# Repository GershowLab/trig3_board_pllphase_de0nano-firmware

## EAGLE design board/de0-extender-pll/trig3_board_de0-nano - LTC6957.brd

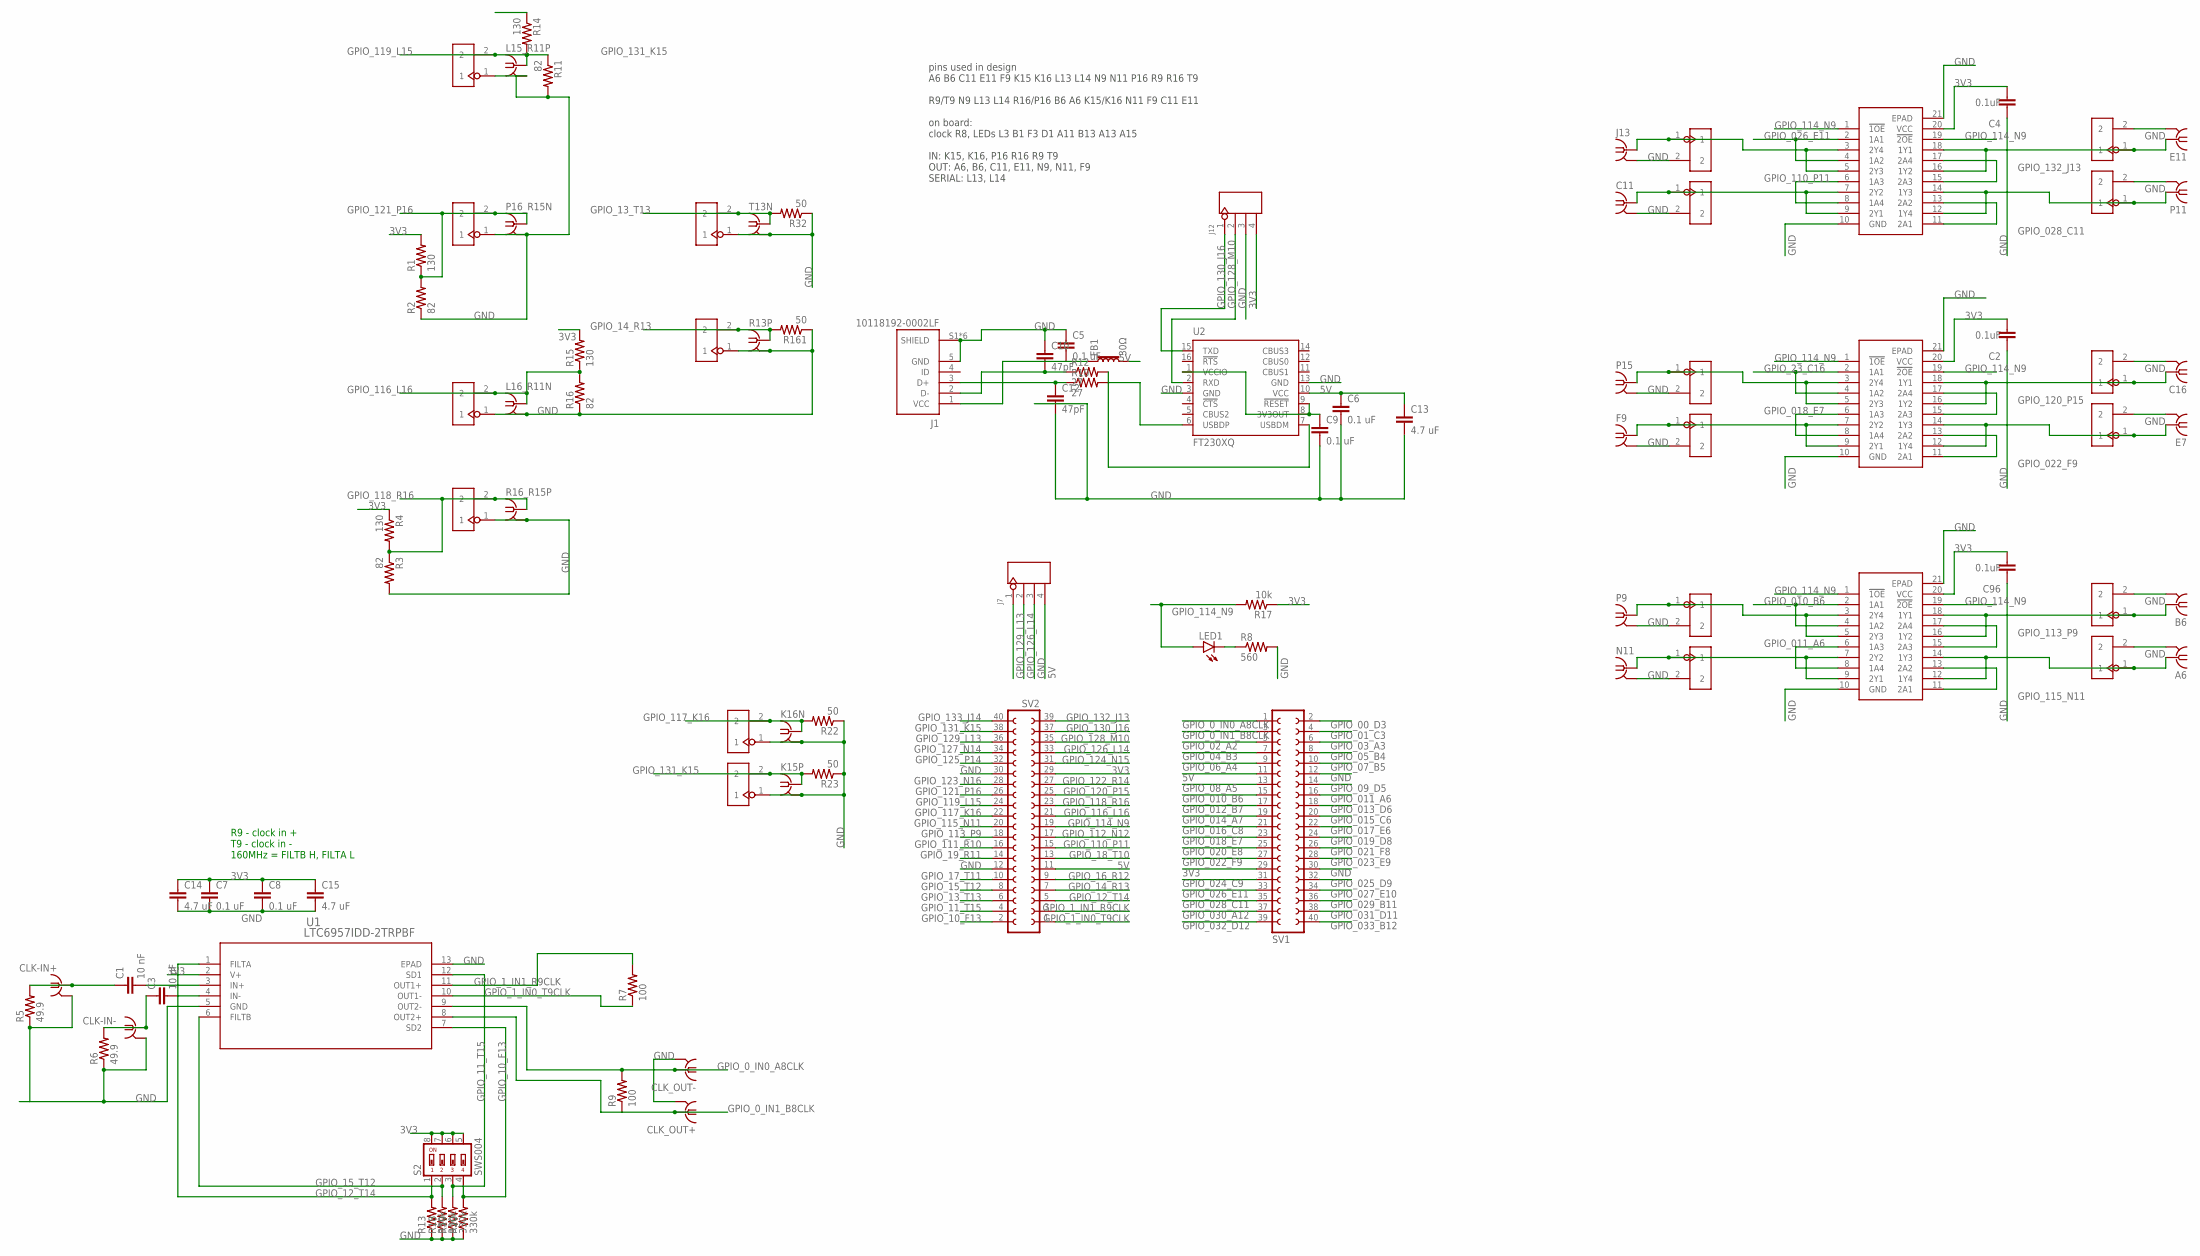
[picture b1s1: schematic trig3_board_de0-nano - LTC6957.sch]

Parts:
A6: BU-SMB-V; LCSC_PART# C496549
B6: BU-SMB-V; LCSC_PART# C496549
C1, C3: 10 nF; C0603; LCSC_PART# C57112
C2, C4, C96: 0.1uF; C0603; LCSC_PART# C14663
C5, C6, C7, C8, C9: 0.1 uF; C0603; LCSC_PART# C14663
C10, C12: 47pF; C0603; LCSC_PART# C1671
C11, C16: BU-SMB-V; LCSC_PART# C496549
C13, C14, C15: 4.7 uF; C0603; LCSC_PART# C19666
CLK-IN+: BU-SMB-V; LCSC_PART# C496549
CLK-IN-: BU-SMB-V; LCSC_PART# C496549
CLK_OUT+: BU-SMB-V; LCSC_PART# C496549
CLK_OUT-: BU-SMB-V; LCSC_PART# C496549
E7, E11: BU-SMB-V; LCSC_PART# C496549
F9: BU-SMB-V; LCSC_PART# C496549
FB1: 30Ω; 0603; LCSC_PART# C1002
J1: 10118192-0002LF; AMPHENOL_10118192-0002LF; LCSC_PART# C132564
J7, J12: 4p-2.54; H4-2.54
J13: BU-SMB-V; LCSC_PART# C496549
J17, J23, J24, J32, J34, J38, J42, J43: 2p-2.54; H2-2.54
K15P, K16N: BU-SMB-V; LCSC_PART# C496549
L15_R11P, L16_R11N: BU-SMB-V; LCSC_PART# C496549
LED1: red; SML0805; LCSC_PART# C84256
N11: BU-SMB-V; LCSC_PART# C496549
OJ41, OJ42, OJ43, OJ44, OJ57, OJ58, OJ59, OJ60, OJ73, OJ74, OJ75, OJ76: 2p-2.54; H2-2.54
P9, P11, P15, P16_R15N: BU-SMB-V; LCSC_PART# C496549
R1, R4, R14, R15: 130; R0603; LCSC_PART# C22796
R2, R3, R11, R16: 82; R0603; LCSC_PART# C23255
R5, R6: 49.9; R0603; LCSC_PART# C23185
R7, R9: 100; R0603; LCSC_PART# C22775
R8: 560; R0805; LCSC_PART# C28636
R10, R12: 27; R0603; LCSC_PART# C25190
R13, R18, R19, R20: 330k; R0603; LCSC_PART# C23137
R13P, R16_R15P: BU-SMB-V; LCSC_PART# C496549
R17: 10k; AXIAL-0.3
R22, R23, R32, R161: 50; AXIAL-0.3
S2: SWS004; SMS-004; LCSC_PART# C221954
SV1, SV2: FE20-2
T13N: BU-SMB-V; LCSC_PART# C496549
U1: LTC6957IDD-2TRPBF; DFN-12_DD_LIT; LCSC_PART# C689878
U2: FT230XQ; QFN16; LCSC_PART# C128629
U3, U4, U5: SN74LVTH244ARGYR; RGY20_3P05X2P05; LCSC_PART# C2869480

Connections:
3V3: C2.2, C4.2, C7.1, C8.1, C14.1, C15.1, C96.2, J12.4, R1.2, R4.1, R14.1, R15.2, R17.P$1 (1), S2.5, S2.6, S2.7, S2.8, SV1.29, SV2.29, U1.2 (V+), U3.20 (VCC), U4.20 (VCC), U5.20 (VCC)
5V: C6.1, C13.1, FB1.2, J7.4, SV1.11, SV2.11, U2.10 (VCC)
GND: A6.2, A6.3 (2), A6.4 (2), A6.5 (2), B6.2, B6.3 (2), B6.4 (2), B6.5 (2), C2.1, C4.1, C5.1, C6.2, C7.2, C8.2, C9.2, C10.1, C11.2, C11.3 (2), C11.4 (2), C11.5 (2), C12.2, C13.2, C14.2, C15.2, C16.2, C16.3 (2), C16.4 (2), C16.5 (2), C96.1, CLK-IN+.2, CLK-IN+.3 (2), CLK-IN+.4 (2), CLK-IN+.5 (2), CLK-IN-.2, CLK-IN-.3 (2), CLK-IN-.4 (2), CLK-IN-.5 (2), CLK_OUT+.2, CLK_OUT+.3 (2), CLK_OUT+.4 (2), CLK_OUT+.5 (2), CLK_OUT-.2, CLK_OUT-.3 (2), CLK_OUT-.4 (2), CLK_OUT-.5 (2), E7.2, E7.3 (2), E7.4 (2), E7.5 (2), E11.2, E11.3 (2), E11.4 (2), E11.5 (2), F9.2, F9.3 (2), F9.4 (2), F9.5 (2), J1.5 (GND), J1.S1 (SHIELD), J1.S2 (SHIELD), J1.S3 (SHIELD), J1.S4 (SHIELD), J1.S5 (SHIELD), J1.S6 (SHIELD), J7.3, J12.3, J13.2, J13.3 (2), J13.4 (2), J13.5 (2), J17.1, J23.1, J24.1, J32.1, J34.1, J38.1, J42.1, J43.1, K15P.2, K15P.3 (2), K15P.4 (2), K15P.5 (2), K16N.2, K16N.3 (2), K16N.4 (2), K16N.5 (2), L15_R11P.2, L15_R11P.3 (2), L15_R11P.4 (2), L15_R11P.5 (2), L16_R11N.2, L16_R11N.3 (2), L16_R11N.4 (2), L16_R11N.5 (2), N11.2, N11.3 (2), N11.4 (2), N11.5 (2), OJ41.2, OJ42.2, OJ43.2, OJ44.2, OJ57.2, OJ58.2, OJ59.2, OJ60.2, OJ73.2, OJ74.2, OJ75.2, OJ76.2, P9.2, P9.3 (2), P9.4 (2), P9.5 (2), P11.2, P11.3 (2), P11.4 (2), P11.5 (2), P15.2, P15.3 (2), P15.4 (2), P15.5 (2), P16_R15N.2, P16_R15N.3 (2), P16_R15N.4 (2), P16_R15N.5 (2), R2.1, R3.2, R5.1, R6.1, R8.2, R11.2, R13.1, R13P.2, R13P.3 (2), R13P.4 (2), R13P.5 (2), R16.1, R16_R15P.2, R16_R15P.3 (2), R16_R15P.4 (2), R16_R15P.5 (2), R18.1, R19.1, R20.1, R22.P$1 (1), R23.P$1 (1), R32.P$1 (1), R161.P$1 (1), SV1.12, SV1.30, SV2.12, SV2.30, T13N.2, T13N.3 (2), T13N.4 (2), T13N.5 (2), U1.5 (GND), U1.13 (EPAD), U2.3 (GND), U2.13 (GND), U3.10 (GND), U3.21 (EPAD), U4.10 (GND), U4.21 (EPAD), U5.10 (GND), U5.21 (EPAD)
GPIO_00_D3: SV1.2
GPIO_0_IN0_A8CLK: CLK_OUT-.1, R9.2, SV1.1, U1.9 (OUT2-)
GPIO_0_IN1_B8CLK: CLK_OUT+.1, R9.1, SV1.3, U1.8 (OUT2+)
GPIO_01_C3: SV1.4
GPIO_1_IN0_T9CLK: R7.1, SV2.1, U1.10 (OUT1-)
GPIO_1_IN1_R9CLK: R7.2, SV2.3, U1.11 (OUT1+)
GPIO_02_A2: SV1.5
GPIO_03_A3: SV1.6
GPIO_04_B3: SV1.7
GPIO_05_B4: SV1.8
GPIO_06_A4: SV1.9
GPIO_07_B5: SV1.10
GPIO_08_A5: SV1.13
GPIO_09_D5: SV1.14
GPIO_010_B6: SV1.15, U5.2 (1A1), U5.4 (1A2)
GPIO_10_F13: R20.2, S2.4, SV2.2, U1.7 (SD2)
GPIO_011_A6: SV1.16, U5.6 (1A3), U5.8 (1A4)
GPIO_11_T15: R19.2, S2.3, SV2.4, U1.12 (SD1)
GPIO_012_B7: SV1.17
GPIO_12_T14: R13.2, S2.1, SV2.5, U1.1 (FILTA)
GPIO_013_D6: SV1.18
GPIO_13_T13: J38.2, R32.P$2 (2), SV2.6, T13N.1
GPIO_014_A7: SV1.19
GPIO_14_R13: J17.2, R13P.1, R161.P$2 (2), SV2.7
GPIO_015_C6: SV1.20
GPIO_15_T12: R18.2, S2.2, SV2.8, U1.6 (FILTB)
GPIO_016_C8: SV1.21
GPIO_16_R12: SV2.9
GPIO_017_E6: SV1.22
GPIO_17_T11: SV2.10
GPIO_018_E7: SV1.23, U4.6 (1A3), U4.8 (1A4)
GPIO_18_T10: SV2.13
GPIO_019_D8: SV1.24
GPIO_19_R11: SV2.14
GPIO_020_E8: SV1.25
GPIO_021_F8: SV1.26
GPIO_022_F9: SV1.27, U4.11 (2A1), U4.13 (2A2)
GPIO_23_C16: U4.2 (1A1), U4.4 (1A2)
GPIO_023_E9: SV1.28
GPIO_024_C9: SV1.31
GPIO_025_D9: SV1.32
GPIO_026_E11: SV1.33, U3.2 (1A1), U3.4 (1A2)
GPIO_027_E10: SV1.34
GPIO_028_C11: SV1.35, U3.11 (2A1), U3.13 (2A2)
GPIO_029_B11: SV1.36
GPIO_030_A12: SV1.37
GPIO_031_D11: SV1.38
GPIO_032_D12: SV1.39
GPIO_033_B12: SV1.40
GPIO_110_P11: SV2.15, U3.6 (1A3), U3.8 (1A4)
GPIO_111_R10: SV2.16
GPIO_112_N12: SV2.17
GPIO_113_P9: SV2.18, U5.15 (2A3), U5.17 (2A4)
GPIO_114_N9: LED1.A, R17.P$2 (2), SV2.19, U3.1 (!1OE), U3.19 (!2OE), U4.1 (!1OE), U4.19 (!2OE), U5.1 (!1OE), U5.19 (!2OE)
GPIO_115_N11: SV2.20, U5.11 (2A1), U5.13 (2A2)
GPIO_116_L16: J32.2, L16_R11N.1, R15.1, R16.2, SV2.21
GPIO_117_K16: J23.2, K16N.1, R22.P$2 (2), SV2.22
GPIO_118_R16: J34.2, R3.1, R4.2, R16_R15P.1, SV2.23
GPIO_119_L15: J43.2, L15_R11P.1, R11.1, R14.2, SV2.24
GPIO_120_P15: SV2.25, U4.15 (2A3), U4.17 (2A4)
GPIO_121_P16: J42.2, P16_R15N.1, R1.1, R2.2, SV2.26
GPIO_122_R14: SV2.27
GPIO_123_N16: SV2.28
GPIO_124_N15: SV2.31
GPIO_125_P14: SV2.32
GPIO_126_L14: J7.2, SV2.33
GPIO_127_N14: SV2.34
GPIO_128_M10: J12.2, SV2.35, U2.2 (RXD)
GPIO_129_L13: J7.1, SV2.36
GPIO_130_J16: J12.1, SV2.37, U2.15 (TXD)
GPIO_131_K15: J24.2, K15P.1, R23.P$2 (2), SV2.38
GPIO_132_J13: SV2.39, U3.15 (2A3), U3.17 (2A4)
GPIO_133_J14: SV2.40
unnamed: C1.1, CLK-IN+.1, R5.2
unnamed: C3.1, CLK-IN-.1, R6.2
unnamed: C1.2, U1.3 (IN+)
unnamed: C3.2, U1.4 (IN-)
unnamed: C5.2, FB1.1, J1.1 (VCC)
unnamed: C12.1, J1.3 (D+), R10.1
unnamed: LED1.C, R8.1
unnamed: C10.2, J1.2 (D-), R12.1
unnamed: R10.2, U2.6 (USBDP)
unnamed: R12.2, U2.7 (USBDM)
unnamed: C9.1, U2.1 (VCCIO), U2.8 (3V3OUT), U2.9 (!RESET)
OUT21: B6.1, OJ44.1, U5.16 (1Y2), U5.18 (1Y1)
OUT22: A6.1, OJ43.1, U5.12 (1Y4), U5.14 (1Y3)
OUT23: OJ41.1, P9.1, U5.3 (2Y4), U5.5 (2Y3)
OUT24: N11.1, OJ42.1, U5.7 (2Y2), U5.9 (2Y1)
OUT29: C16.1, OJ60.1, U4.16 (1Y2), U4.18 (1Y1)
OUT30: E7.1, OJ59.1, U4.12 (1Y4), U4.14 (1Y3)
OUT31: OJ57.1, P15.1, U4.3 (2Y4), U4.5 (2Y3)
OUT32: F9.1, OJ58.1, U4.7 (2Y2), U4.9 (2Y1)
OUT37: E11.1, OJ76.1, U3.16 (1Y2), U3.18 (1Y1)
OUT38: OJ75.1, P11.1, U3.12 (1Y4), U3.14 (1Y3)
OUT39: J13.1, OJ73.1, U3.3 (2Y4), U3.5 (2Y3)
OUT40: C11.1, OJ74.1, U3.7 (2Y2), U3.9 (2Y1)

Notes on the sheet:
pins used in design A6 B6 C11 E11 F9 K15 K16 L13 L14 N9 N11 P16 R9 R16 T9 R9/T9 N9 L13 L14 R16/P16 B6 A6 K15/K16 N11 F9 C11 E11 on board: clock R8, LEDs L3 B1 F3 D1 A11 B13 A13 A15 IN: K15, K16, P16 R16 R9 T9 OUT: A6, B6, C11, E11, N9, N11, F9 SERIAL: L13, L14
R9 - clock in + T9 - clock in - 160MHz = FILTB H, FILTA L

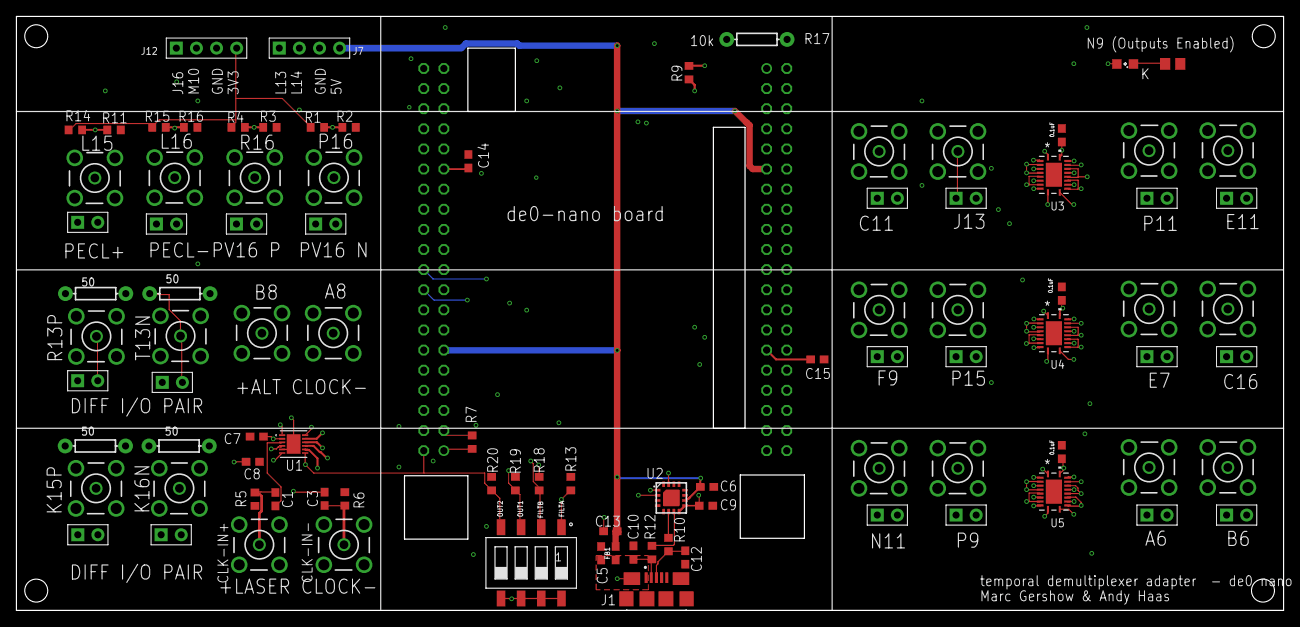
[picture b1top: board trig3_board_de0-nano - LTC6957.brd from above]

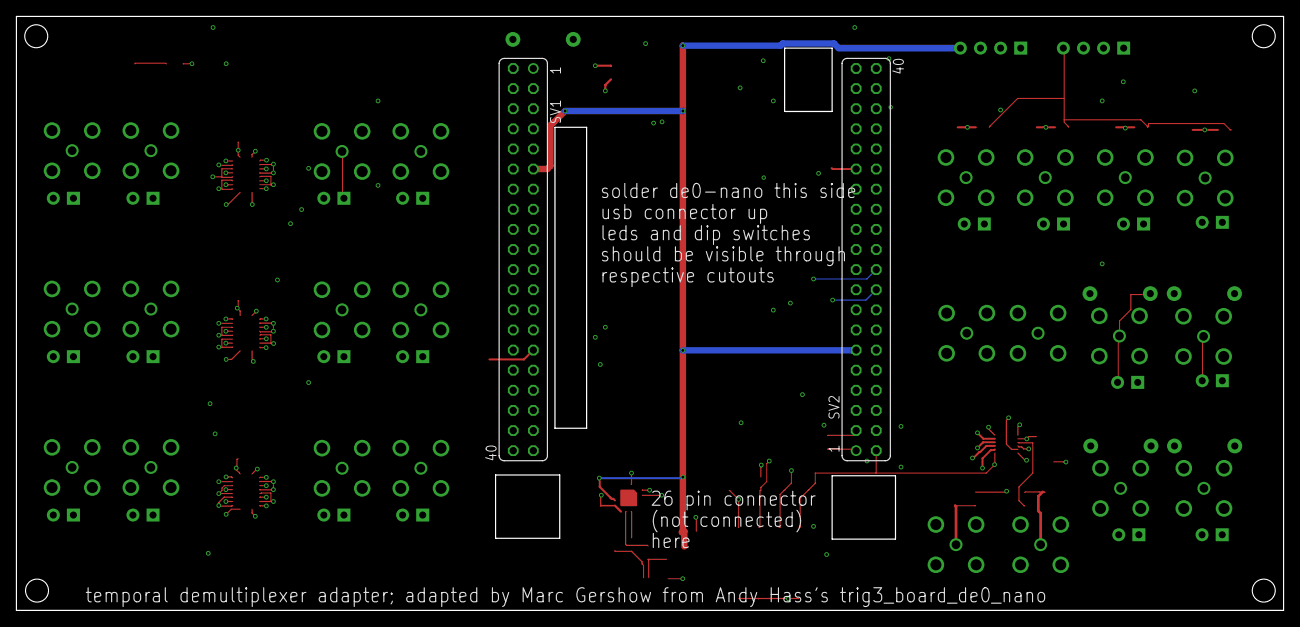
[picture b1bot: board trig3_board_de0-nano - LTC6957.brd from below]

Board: 4 copper layers, 160.0 x 75.0 mm, 96 parts (2 on the bottom side), 59 nets.

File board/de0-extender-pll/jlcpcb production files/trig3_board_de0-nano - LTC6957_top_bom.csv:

Comment,Designator,Footprint,LCSC Part #
0.1 uF,C5 C6 C7 C8 C9,C0603,C14663
0.1uF,C2 C4 C96,C0603,C14663
2p-2.54,J17 J23 J24 J32 J34 J38 J42 J43 OJ41 OJ42 OJ43 OJ44 OJ57 OJ58 OJ59 OJ60 OJ73 OJ74 OJ75 OJ76,H2-2.54,
4.7 uF,C13 C14 C15,C0603,C19666
4p-2.54,J7 J12,H4-2.54,
10 nF,C1 C3,C0603,C57112
10k,R17,AXIAL-0.3,
27,R10 R12,R0603,C25190
30Ω,FB1,0603,C1002
47pF,C10 C12,C0603,C1671
49.9,R5 R6,R0603,C23185
50,R22 R23 R32 R161,AXIAL-0.3,
82,R2 R3 R11 R16,R0603,C23255
100,R7 R9,R0603,C22775
130,R1 R4 R14 R15,R0603,C22796
330k,R13 R18 R19 R20,R0603,C23137
560,R8,R0805,C28636
10118192-0002LF,J1,AMPHENOL_10118192-0002LF,C132564
BU-SMB-V,A6 B6 C11 C16 CLK-IN+ CLK-IN- CLK_OUT+ CLK_OUT- E7 E11 F9 J13 K15P K16N L15_R11P L16_R11N N11 P9 P11 P15 P16_R15N R13P R16_R15P T13N,BU-SMB-V,C496549
FT230XQ,U2,QFN16,C128629
LTC6957IDD-2TRPBF,U1,DFN-12_DD_LIT,C689878
SN74LVTH244ARGYR,U3 U4 U5,RGY20_3P05X2P05,C2869480
SWS004,S2,SMS-004,C221954
red,LED1,SML0805,C84256

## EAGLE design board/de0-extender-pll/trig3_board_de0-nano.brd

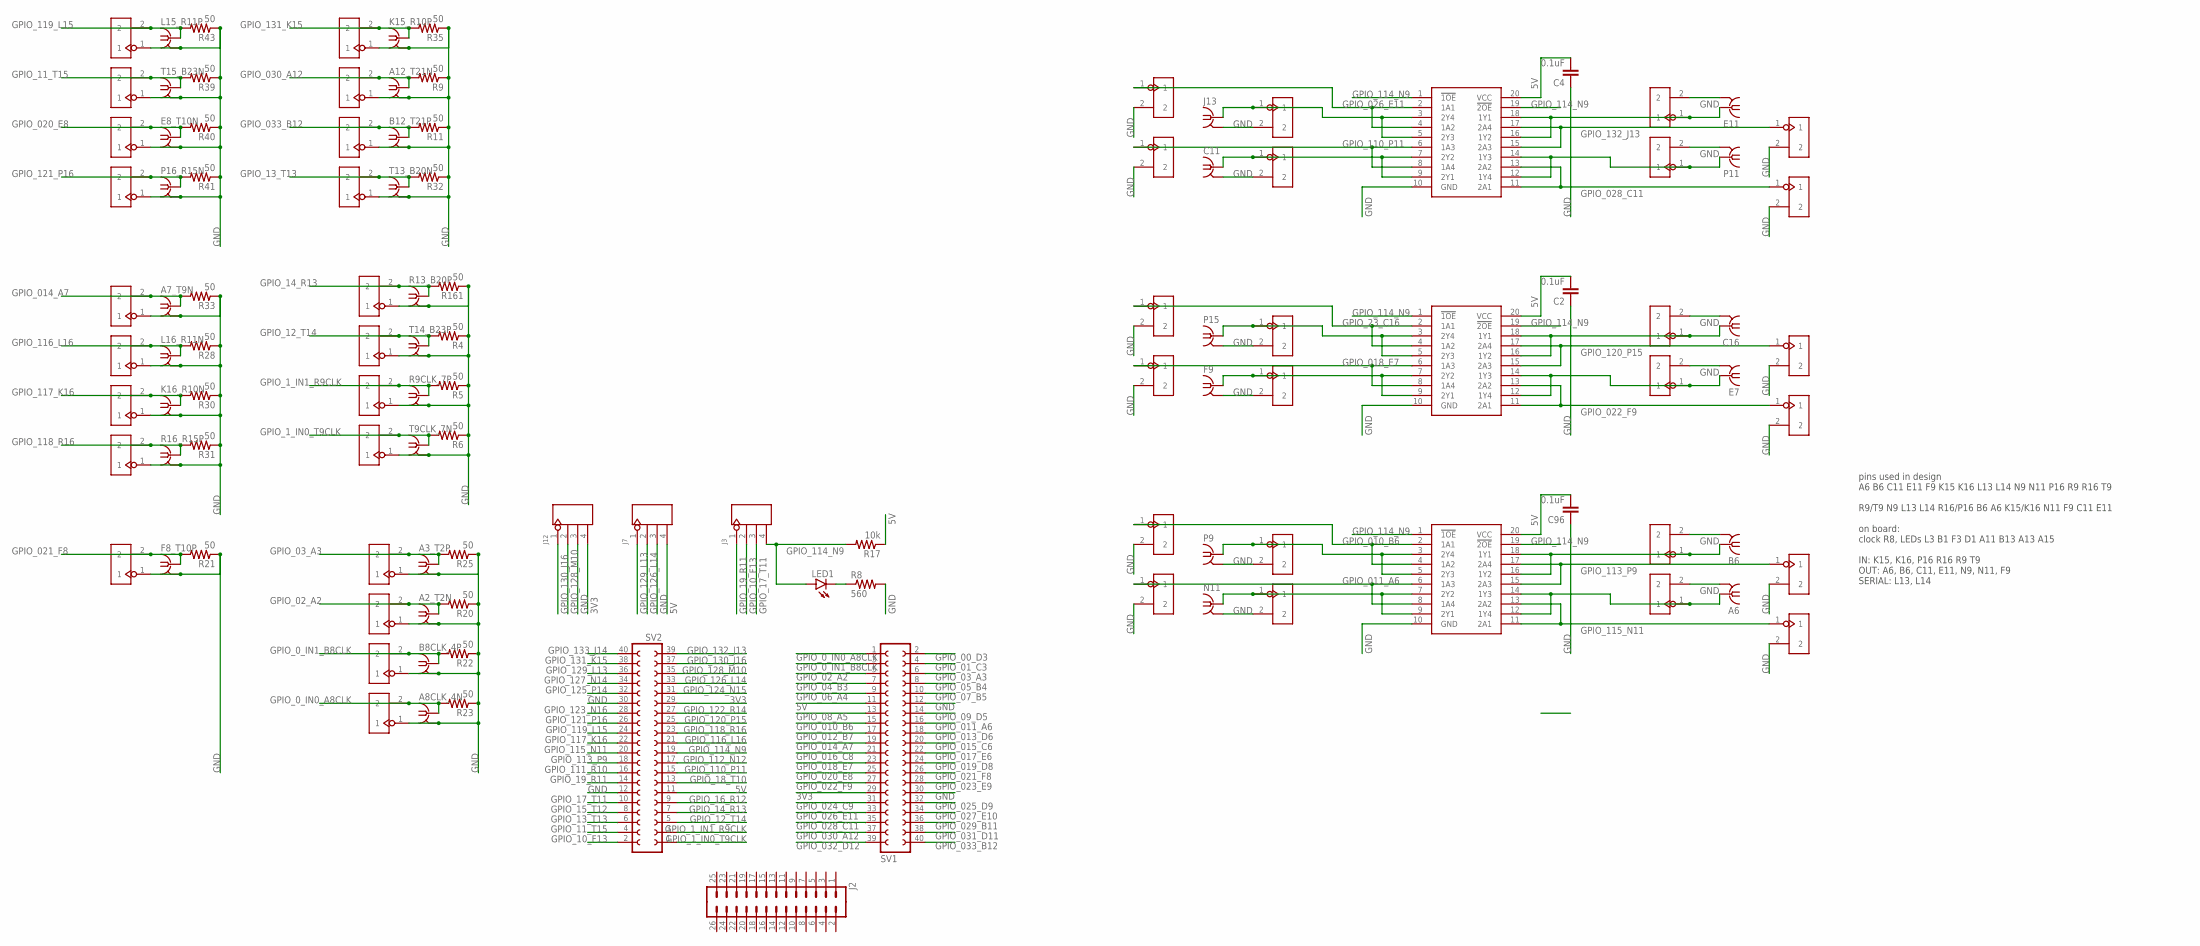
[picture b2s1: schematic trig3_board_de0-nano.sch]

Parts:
A2_T2N, A3_T2P, A6, A7_T9N, A8CLK_4N, A12_T21N: BU-SMB-V
B6, B8CLK_4P, B12_T21P: BU-SMB-V
C2, C4, C96: 0.1uF; 0805
C11, C16: BU-SMB-V
E7, E8_T10N, E11: BU-SMB-V
F8_T10P, F9: BU-SMB-V
J2: M13X22X13; 2X13
J3, J7, J12: 4p-2.54; H4-2.54
J4, J5, J6, J17, J18, J22, J23, J24, J25, J32, J33, J34, J35, J36, J37, J38, J39, J40, J41, J42, J43: 2p-2.54; H2-2.54
J13: BU-SMB-V
K15_R10P, K16_R10N: BU-SMB-V
L15_R11P, L16_R11N: BU-SMB-V
LED1: red; CHIP-LED0805
N11: BU-SMB-V
OJ41, OJ42, OJ43, OJ44, OJ45, OJ46, OJ47, OJ48, OJ57, OJ58, OJ59, OJ60, OJ61, OJ62, OJ63, OJ64, OJ73, OJ74, OJ75, OJ76, OJ77, OJ78, OJ79, OJ80: 2p-2.54; H2-2.54
P9, P11, P15, P16_R15N: BU-SMB-V
R4, R5, R6, R9, R11, R20, R21, R22, R23, R25, R28, R30, R31, R32, R33, R35, R39, R40, R41, R43, R161: 50; AXIAL-0.3
R8: 560; R0805
R9CLK_7P, R13_B20P, R16_R15P: BU-SMB-V
R17: 10k; AXIAL-0.3
SV1, SV2: FE20-2
T9CLK_7N, T13_B20N, T14_B23P, T15_B23N: BU-SMB-V
VSLUE5, VSLUE7, VSLUE9: SN74ACT244DW; SOIC127P1030X265-20N

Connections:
3V3: J12.4, SV1.29, SV2.29
5V: C2.2, C4.2, C96.2, J7.4, R17.P$1 (1), SV1.11, SV2.11, VSLUE5.20 (VCC), VSLUE7.20 (VCC), VSLUE9.20 (VCC)
GND: A2_T2N.2, A2_T2N.3 (2), A2_T2N.4 (2), A2_T2N.5 (2), A3_T2P.2, A3_T2P.3 (2), A3_T2P.4 (2), A3_T2P.5 (2), A6.2, A6.3 (2), A6.4 (2), A6.5 (2), A7_T9N.2, A7_T9N.3 (2), A7_T9N.4 (2), A7_T9N.5 (2), A8CLK_4N.2, A8CLK_4N.3 (2), A8CLK_4N.4 (2), A8CLK_4N.5 (2), A12_T21N.2, A12_T21N.3 (2), A12_T21N.4 (2), A12_T21N.5 (2), B6.2, B6.3 (2), B6.4 (2), B6.5 (2), B8CLK_4P.2, B8CLK_4P.3 (2), B8CLK_4P.4 (2), B8CLK_4P.5 (2), B12_T21P.2, B12_T21P.3 (2), B12_T21P.4 (2), B12_T21P.5 (2), C2.1, C4.1, C11.2, C11.3 (2), C11.4 (2), C11.5 (2), C16.2, C16.3 (2), C16.4 (2), C16.5 (2), C96.1, E7.2, E7.3 (2), E7.4 (2), E7.5 (2), E8_T10N.2, E8_T10N.3 (2), E8_T10N.4 (2), E8_T10N.5 (2), E11.2, E11.3 (2), E11.4 (2), E11.5 (2), F8_T10P.2, F8_T10P.3 (2), F8_T10P.4 (2), F8_T10P.5 (2), F9.2, F9.3 (2), F9.4 (2), F9.5 (2), J4.1, J5.1, J6.1, J7.3, J12.3, J13.2, J13.3 (2), J13.4 (2), J13.5 (2), J17.1, J18.1, J22.1, J23.1, J24.1, J25.1, J32.1, J33.1, J34.1, J35.1, J36.1, J37.1, J38.1, J39.1, J40.1, J41.1, J42.1, J43.1, K15_R10P.2, K15_R10P.3 (2), K15_R10P.4 (2), K15_R10P.5 (2), K16_R10N.2, K16_R10N.3 (2), K16_R10N.4 (2), K16_R10N.5 (2), L15_R11P.2, L15_R11P.3 (2), L15_R11P.4 (2), L15_R11P.5 (2), L16_R11N.2, L16_R11N.3 (2), L16_R11N.4 (2), L16_R11N.5 (2), N11.2, N11.3 (2), N11.4 (2), N11.5 (2), OJ41.2, OJ42.2, OJ43.2, OJ44.2, OJ45.2, OJ46.2, OJ47.2, OJ48.2, OJ57.2, OJ58.2, OJ59.2, OJ60.2, OJ61.2, OJ62.2, OJ63.2, OJ64.2, OJ73.2, OJ74.2, OJ75.2, OJ76.2, OJ77.2, OJ78.2, OJ79.2, OJ80.2, P9.2, P9.3 (2), P9.4 (2), P9.5 (2), P11.2, P11.3 (2), P11.4 (2), P11.5 (2), P15.2, P15.3 (2), P15.4 (2), P15.5 (2), P16_R15N.2, P16_R15N.3 (2), P16_R15N.4 (2), P16_R15N.5 (2), R4.P$1 (1), R5.P$1 (1), R6.P$1 (1), R8.2, R9.P$1 (1), R9CLK_7P.2, R9CLK_7P.3 (2), R9CLK_7P.4 (2), R9CLK_7P.5 (2), R11.P$1 (1), R13_B20P.2, R13_B20P.3 (2), R13_B20P.4 (2), R13_B20P.5 (2), R16_R15P.2, R16_R15P.3 (2), R16_R15P.4 (2), R16_R15P.5 (2), R20.P$1 (1), R21.P$1 (1), R22.P$1 (1), R23.P$1 (1), R25.P$1 (1), R28.P$1 (1), R30.P$1 (1), R31.P$1 (1), R32.P$1 (1), R33.P$1 (1), R35.P$1 (1), R39.P$1 (1), R40.P$1 (1), R41.P$1 (1), R43.P$1 (1), R161.P$1 (1), SV1.12, SV1.30, SV2.12, SV2.30, T9CLK_7N.2, T9CLK_7N.3 (2), T9CLK_7N.4 (2), T9CLK_7N.5 (2), T13_B20N.2, T13_B20N.3 (2), T13_B20N.4 (2), T13_B20N.5 (2), T14_B23P.2, T14_B23P.3 (2), T14_B23P.4 (2), T14_B23P.5 (2), T15_B23N.2, T15_B23N.3 (2), T15_B23N.4 (2), T15_B23N.5 (2), VSLUE5.10 (GND), VSLUE7.10 (GND), VSLUE9.10 (GND)
GPIO_00_D3: SV1.2
GPIO_0_IN0_A8CLK: A8CLK_4N.1, J24.2, R23.P$2 (2), SV1.1
GPIO_0_IN1_B8CLK: B8CLK_4P.1, J23.2, R22.P$2 (2), SV1.3
GPIO_01_C3: SV1.4
GPIO_1_IN0_T9CLK: J6.2, R6.P$2 (2), SV2.1, T9CLK_7N.1
GPIO_1_IN1_R9CLK: J5.2, R5.P$2 (2), R9CLK_7P.1, SV2.3
GPIO_02_A2: A2_T2N.1, J22.2, R20.P$2 (2), SV1.5
GPIO_03_A3: A3_T2P.1, J25.2, R25.P$2 (2), SV1.6
GPIO_04_B3: SV1.7
GPIO_05_B4: SV1.8
GPIO_06_A4: SV1.9
GPIO_07_B5: SV1.10
GPIO_08_A5: SV1.13
GPIO_09_D5: SV1.14
GPIO_010_B6: OJ47.1, SV1.15, VSLUE5.2 (1A1), VSLUE5.4 (1A2)
GPIO_10_F13: J3.2, SV2.2
GPIO_011_A6: OJ48.1, SV1.16, VSLUE5.6 (1A3), VSLUE5.8 (1A4)
GPIO_11_T15: J40.2, R39.P$2 (2), SV2.4, T15_B23N.1
GPIO_012_B7: SV1.17
GPIO_12_T14: J4.2, R4.P$2 (2), SV2.5, T14_B23P.1
GPIO_013_D6: SV1.18
GPIO_13_T13: J38.2, R32.P$2 (2), SV2.6, T13_B20N.1
GPIO_014_A7: A7_T9N.1, J35.2, R33.P$2 (2), SV1.19
GPIO_14_R13: J17.2, R13_B20P.1, R161.P$2 (2), SV2.7
GPIO_015_C6: SV1.20
GPIO_15_T12: SV2.8
GPIO_016_C8: SV1.21
GPIO_16_R12: SV2.9
GPIO_017_E6: SV1.22
GPIO_17_T11: J3.3, SV2.10
GPIO_018_E7: OJ64.1, SV1.23, VSLUE7.6 (1A3), VSLUE7.8 (1A4)
GPIO_18_T10: SV2.13
GPIO_019_D8: SV1.24
GPIO_19_R11: J3.1, SV2.14
GPIO_020_E8: E8_T10N.1, J41.2, R40.P$2 (2), SV1.25
GPIO_021_F8: F8_T10P.1, J18.2, R21.P$2 (2), SV1.26
GPIO_022_F9: OJ62.1, SV1.27, VSLUE7.11 (2A1), VSLUE7.13 (2A2)
GPIO_23_C16: OJ63.1, VSLUE7.2 (1A1), VSLUE7.4 (1A2)
GPIO_023_E9: SV1.28
GPIO_024_C9: SV1.31
GPIO_025_D9: SV1.32
GPIO_026_E11: OJ79.1, SV1.33, VSLUE9.2 (1A1), VSLUE9.4 (1A2)
GPIO_027_E10: SV1.34
GPIO_028_C11: OJ78.1, SV1.35, VSLUE9.11 (2A1), VSLUE9.13 (2A2)
GPIO_029_B11: SV1.36
GPIO_030_A12: A12_T21N.1, J36.2, R9.P$2 (2), SV1.37
GPIO_031_D11: SV1.38
GPIO_032_D12: SV1.39
GPIO_033_B12: B12_T21P.1, J37.2, R11.P$2 (2), SV1.40
GPIO_110_P11: OJ80.1, SV2.15, VSLUE9.6 (1A3), VSLUE9.8 (1A4)
GPIO_111_R10: SV2.16
GPIO_112_N12: SV2.17
GPIO_113_P9: OJ45.1, SV2.18, VSLUE5.15 (2A3), VSLUE5.17 (2A4)
GPIO_114_N9: J3.4, LED1.A, R17.P$2 (2), SV2.19, VSLUE5.1 (!1OE), VSLUE5.19 (!2OE), VSLUE7.1 (!1OE), VSLUE7.19 (!2OE), VSLUE9.1 (!1OE), VSLUE9.19 (!2OE)
GPIO_115_N11: OJ46.1, SV2.20, VSLUE5.11 (2A1), VSLUE5.13 (2A2)
GPIO_116_L16: J32.2, L16_R11N.1, R28.P$2 (2), SV2.21
GPIO_117_K16: J33.2, K16_R10N.1, R30.P$2 (2), SV2.22
GPIO_118_R16: J34.2, R16_R15P.1, R31.P$2 (2), SV2.23
GPIO_119_L15: J43.2, L15_R11P.1, R43.P$2 (2), SV2.24
GPIO_120_P15: OJ61.1, SV2.25, VSLUE7.15 (2A3), VSLUE7.17 (2A4)
GPIO_121_P16: J42.2, P16_R15N.1, R41.P$2 (2), SV2.26
GPIO_122_R14: SV2.27
GPIO_123_N16: SV2.28
GPIO_124_N15: SV2.31
GPIO_125_P14: SV2.32
GPIO_126_L14: J7.2, SV2.33
GPIO_127_N14: SV2.34
GPIO_128_M10: J12.2, SV2.35
GPIO_129_L13: J7.1, SV2.36
GPIO_130_J16: J12.1, SV2.37
GPIO_131_K15: J39.2, K15_R10P.1, R35.P$2 (2), SV2.38
GPIO_132_J13: OJ77.1, SV2.39, VSLUE9.15 (2A3), VSLUE9.17 (2A4)
GPIO_133_J14: SV2.40
unnamed: LED1.C, R8.1
OUT21: B6.1, OJ44.1, VSLUE5.16 (1Y2), VSLUE5.18 (1Y1)
OUT22: A6.1, OJ43.1, VSLUE5.12 (1Y4), VSLUE5.14 (1Y3)
OUT23: OJ41.1, P9.1, VSLUE5.3 (2Y4), VSLUE5.5 (2Y3)
OUT24: N11.1, OJ42.1, VSLUE5.7 (2Y2), VSLUE5.9 (2Y1)
OUT29: C16.1, OJ60.1, VSLUE7.16 (1Y2), VSLUE7.18 (1Y1)
OUT30: E7.1, OJ59.1, VSLUE7.12 (1Y4), VSLUE7.14 (1Y3)
OUT31: OJ57.1, P15.1, VSLUE7.3 (2Y4), VSLUE7.5 (2Y3)
OUT32: F9.1, OJ58.1, VSLUE7.7 (2Y2), VSLUE7.9 (2Y1)
OUT37: E11.1, OJ76.1, VSLUE9.16 (1Y2), VSLUE9.18 (1Y1)
OUT38: OJ75.1, P11.1, VSLUE9.12 (1Y4), VSLUE9.14 (1Y3)
OUT39: J13.1, OJ73.1, VSLUE9.3 (2Y4), VSLUE9.5 (2Y3)
OUT40: C11.1, OJ74.1, VSLUE9.7 (2Y2), VSLUE9.9 (2Y1)

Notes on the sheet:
pins used in design A6 B6 C11 E11 F9 K15 K16 L13 L14 N9 N11 P16 R9 R16 T9 R9/T9 N9 L13 L14 R16/P16 B6 A6 K15/K16 N11 F9 C11 E11 on board: clock R8, LEDs L3 B1 F3 D1 A11 B13 A13 A15 IN: K15, K16, P16 R16 R9 T9 OUT: A6, B6, C11, E11, N9, N11, F9 SERIAL: L13, L14

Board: 4 copper layers, 114 parts (2 on the bottom side), 57 nets, no tracks yet.

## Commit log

2022-04-27 Update pmt demultiplexer control.vi
    changed default phase and bin width
2023-11-15 annotating firmware, working on board
2023-11-15 removed some unused inputs
    kept all clock inputs and some extra inputs
2023-11-15 removed many outputs and negative voltage
2023-11-15 more removal
2023-11-16 going to delete more ins/outs
2023-11-16 reduced board ready for autoroute
    creating board with ltc carrier now
2023-11-22 ltc6957 based board starting
2023-11-27 fixed pecl termination
2023-12-01 more work on board
2023-12-02 ready to autoroute
2023-12-02 autoroute attempt 2
2023-12-02 removed unnecessary header
2023-12-02 routed - now needs aesthetic cleanup
2023-12-03 fixed auto-router top layer nonsense
2023-12-04 removed wire stubs, tried to fix package rotation
    rotated footprints in library but change did not propagate to pcb
2023-12-04 rotated footprints and cosmetic updates to board
2023-12-04 ready for ordering
    will probably need to do one last check
2023-12-05 fixed usb connection error; changed connector; change dip switch part
    added sd1, sd2, filta, filtb to gpio pins also
2023-12-05 modified silksccreen
2023-12-06 one change to silkscreen; added 4.7 uF capacitors to 3.3V header connections
2023-12-06 changed via hole size to reduce costs
2023-12-19 connected dip switches on carrier to outputs in code
    lots of warnings on compilation now, presumably related to version upgrade of quartus
    ---
    SW version 29
2023-12-22 disabled onboard clock and change laser clock source to B8/A8

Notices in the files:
parts and their libraries:
SparkFun-Passives: Licensing: Creative Commons ShareAlike 4.0 International - https://creativecommons.org/licenses/by-sa/4.0
COPYRIGHT: Copyright (C) 2023 Ultra Librarian. All rights reserved.
